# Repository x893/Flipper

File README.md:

# Flipper
Projects for FlipperZero

CadSoft Eagle

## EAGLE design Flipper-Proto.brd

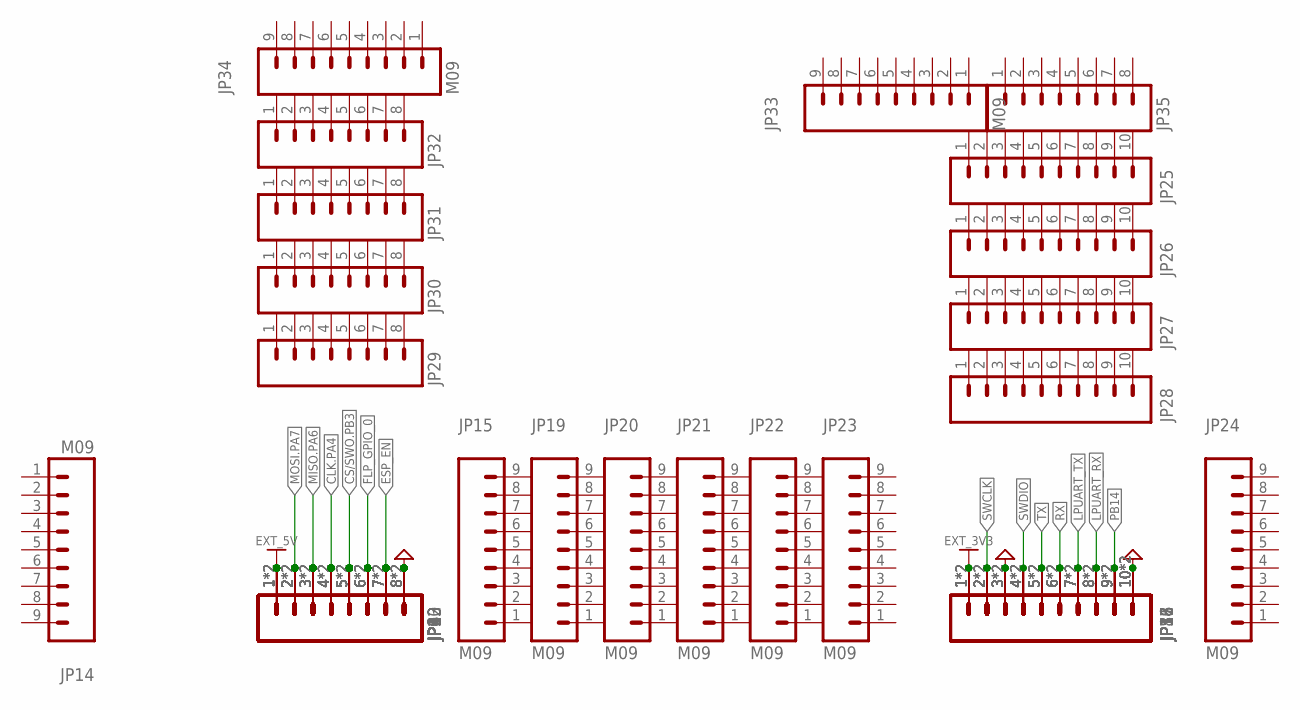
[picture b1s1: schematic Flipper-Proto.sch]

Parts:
JP1, JP11, JP16, JP17, JP18, JP25, JP26, JP27, JP28: M10"; 1X10
JP2, JP3, JP4: M08SMD-COMBO; 1X08_SMD_COMBINED
JP5, JP7, JP8: M10COMBINED; 1X10_SMD_COMBINED
JP6, JP9, JP10, JP12, JP13, JP29, JP30, JP31, JP32, JP35: M081X08; 1X08
JP14, JP15, JP19, JP20, JP21, JP22, JP23, JP24, JP33, JP34: M09; 1X09

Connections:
CLK.PA4: JP2.4, JP2.4@2 (4), JP3.4, JP3.4@2 (4), JP4.4, JP4.4@2 (4), JP6.4, JP9.4, JP10.4, JP12.4, JP13.4
CS/SWO.PB3: JP2.5, JP2.5@2 (5), JP3.5, JP3.5@2 (5), JP4.5, JP4.5@2 (5), JP6.5, JP9.5, JP10.5, JP12.5, JP13.5
ESP_EN: JP2.7, JP2.7@2 (7), JP3.7, JP3.7@2 (7), JP4.7, JP4.7@2 (7), JP6.7, JP9.7, JP10.7, JP12.7, JP13.7
EXT_3V3: JP1.1, JP5.1, JP5.1@2 (1), JP7.1, JP7.1@2 (1), JP8.1, JP8.1@2 (1), JP11.1, JP16.1, JP17.1, JP18.1
EXT_5V: JP2.1, JP2.1@2 (1), JP3.1, JP3.1@2 (1), JP4.1, JP4.1@2 (1), JP6.1, JP9.1, JP10.1, JP12.1, JP13.1
FLP_GPIO_0: JP2.6, JP2.6@2 (6), JP3.6, JP3.6@2 (6), JP4.6, JP4.6@2 (6), JP6.6, JP9.6, JP10.6, JP12.6, JP13.6
GND: JP1.3, JP1.10, JP2.8, JP2.8@2 (8), JP3.8, JP3.8@2 (8), JP4.8, JP4.8@2 (8), JP5.3, JP5.3@2 (3), JP5.10, JP5.10@2 (10), JP6.8, JP7.3, JP7.3@2 (3), JP7.10, JP7.10@2 (10), JP8.3, JP8.3@2 (3), JP8.10, JP8.10@2 (10), JP9.8, JP10.8, JP11.3, JP11.10, JP12.8, JP13.8, JP16.3, JP16.10, JP17.3, JP17.10, JP18.3, JP18.10
LPUART_RX: JP1.8, JP5.8, JP5.8@2 (8), JP7.8, JP7.8@2 (8), JP8.8, JP8.8@2 (8), JP11.8, JP16.8, JP17.8, JP18.8
LPUART_TX: JP1.7, JP5.7, JP5.7@2 (7), JP7.7, JP7.7@2 (7), JP8.7, JP8.7@2 (7), JP11.7, JP16.7, JP17.7, JP18.7
MISO.PA6: JP2.3, JP2.3@2 (3), JP3.3, JP3.3@2 (3), JP4.3, JP4.3@2 (3), JP6.3, JP9.3, JP10.3, JP12.3, JP13.3
MOSI.PA7: JP2.2, JP2.2@2 (2), JP3.2, JP3.2@2 (2), JP4.2, JP4.2@2 (2), JP6.2, JP9.2, JP10.2, JP12.2, JP13.2
PB14: JP1.9, JP5.9, JP5.9@2 (9), JP7.9, JP7.9@2 (9), JP8.9, JP8.9@2 (9), JP11.9, JP16.9, JP17.9, JP18.9
RX: JP1.6, JP5.6, JP5.6@2 (6), JP7.6, JP7.6@2 (6), JP8.6, JP8.6@2 (6), JP11.6, JP16.6, JP17.6, JP18.6
SWCLK: JP1.2, JP5.2, JP5.2@2 (2), JP7.2, JP7.2@2 (2), JP8.2, JP8.2@2 (2), JP11.2, JP16.2, JP17.2, JP18.2
SWDIO: JP1.4, JP5.4, JP5.4@2 (4), JP7.4, JP7.4@2 (4), JP8.4, JP8.4@2 (4), JP11.4, JP16.4, JP17.4, JP18.4
TX: JP1.5, JP5.5, JP5.5@2 (5), JP7.5, JP7.5@2 (5), JP8.5, JP8.5@2 (5), JP11.5, JP16.5, JP17.5, JP18.5

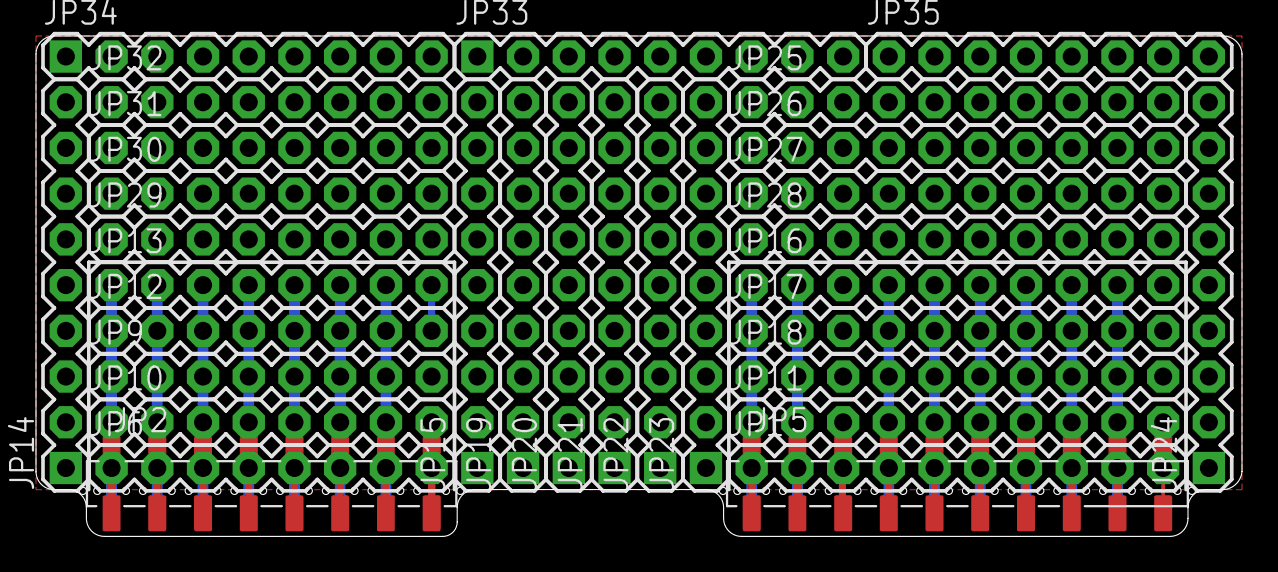
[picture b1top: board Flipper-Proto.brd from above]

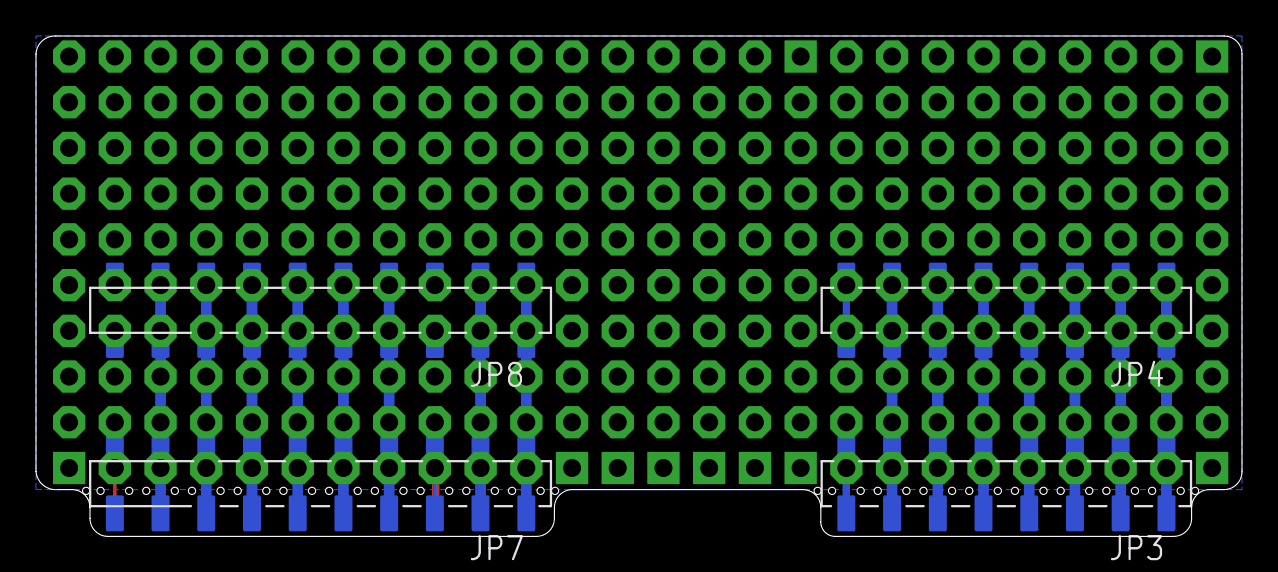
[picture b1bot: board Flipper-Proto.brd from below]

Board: 2 copper layers, 67.0 x 27.8 mm, 35 parts (4 on the bottom side), 16 nets.

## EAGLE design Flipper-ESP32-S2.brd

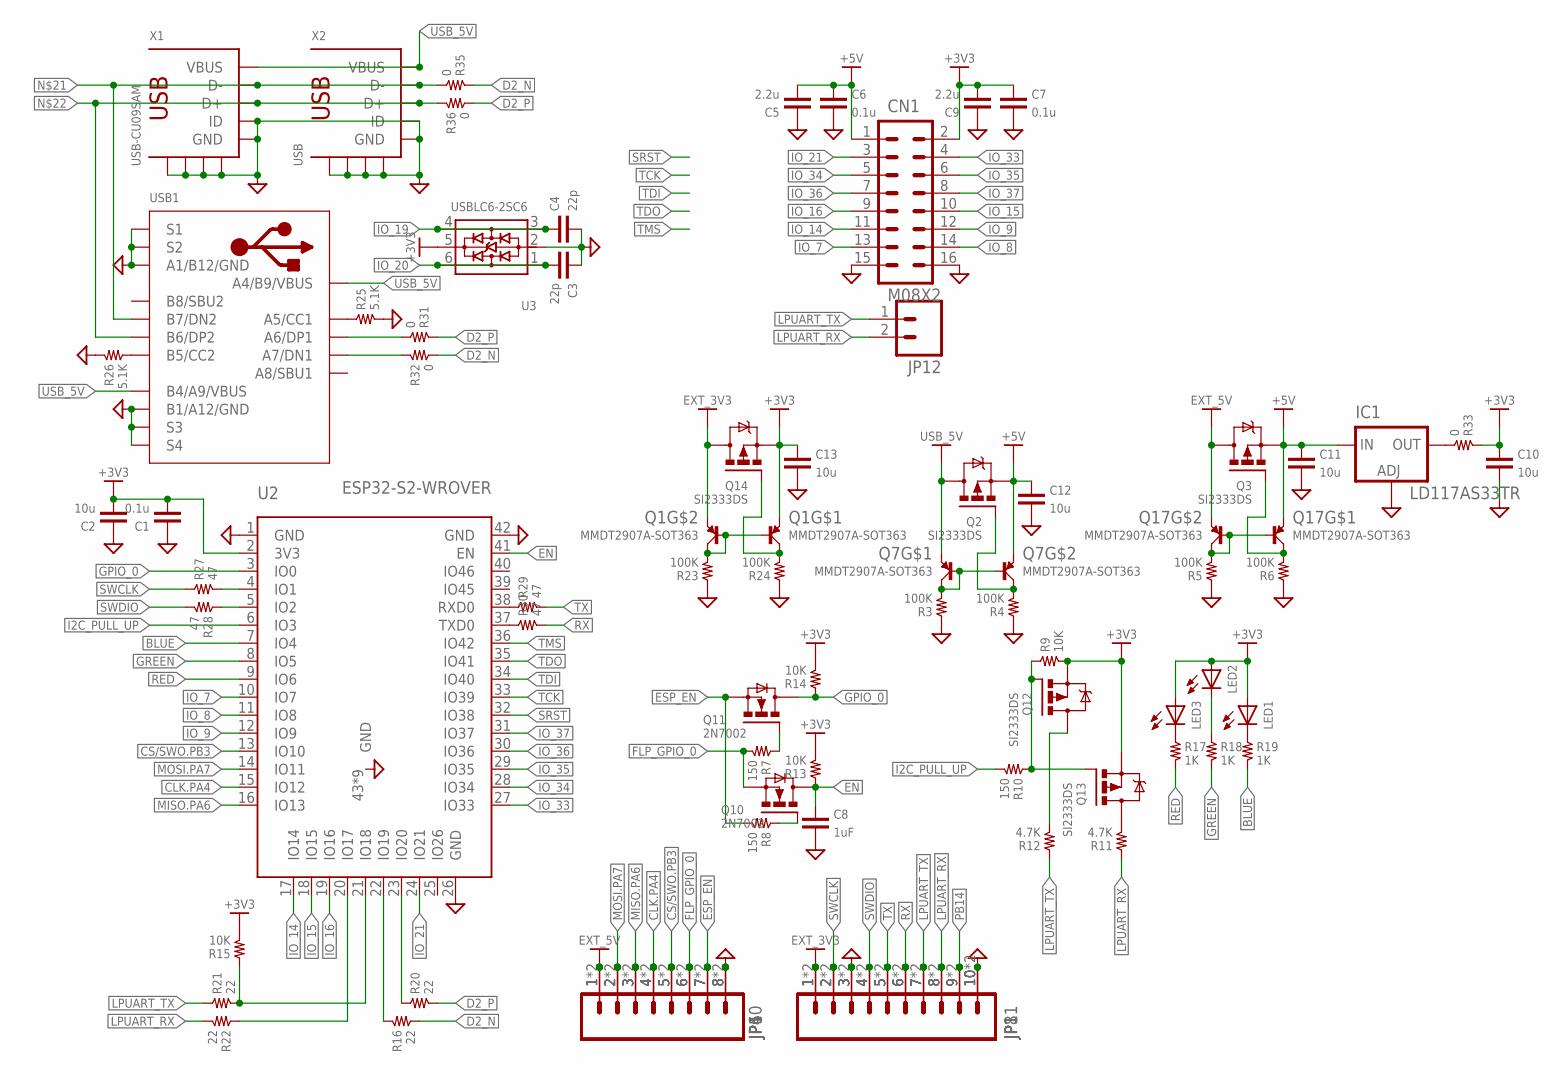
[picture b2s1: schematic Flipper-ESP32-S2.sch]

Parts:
C1, C6, C7: 0.1u; 0603
C2, C10, C11, C12, C13: 10u; 0805
C3, C4: 22p; 0603
C5, C9: 2.2u; 0603
C8: 1uF; 0603
CN1: M08X2; 2X8
IC1: LD117AS33TR; SOT223
JP1, JP11: M10"; 1X10
JP4: M08SMD-COMBO; 1X08_SMD_COMBINED
JP6, JP10: M081X08; 1X08
JP8: M10COMBINED; 1X10_SMD_COMBINED
JP12: M02PTH; 1X02
LED1, LED2, LED3: LEDCHIPLED_0603; CHIPLED_0603
Q1, Q7, Q17: MMDT2907A-SOT363; SOT363
Q2, Q3, Q12, Q13, Q14: SI2333DS; SOT-23
Q10, Q11: 2N7002; SOT-23
R3, R4, R5, R6, R23, R24: 100K; 0603
R7, R8, R10: 150; 0603
R9, R13, R14, R15: 10K; 0603
R11, R12: 4.7K; 0603
R16, R20, R21, R22: 22; 0603
R17, R18, R19: 1K; 0603
R25, R26: 5.1K; 0603
R27, R28, R29, R30: 47; 0603
R31, R32, R33, R35, R36: 0; 0402
U2: ESP32-S2-WROVER
U3: USBLC6-2SC6; SOT23-6
USB1: USB2.0-TYPE-C
X1: USB-CU09SAM; CU09SAM
X2: USB; 473460001

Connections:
5V: C5.1, C6.2, C11.2, C12.2, CN1.1, IC1.3 (IN), Q2.2 (S), Q3.2 (S), Q7.4 (E), Q17.1 (E)
+3V3: C1.1, C2.1, C7.2, C9.1, C10.2, C13.2, CN1.2, LED1.A, LED2.A, LED3.A, Q1.1 (E), Q12.2 (S), Q13.2 (S), Q14.2 (S), R9.2, R13.2, R14.2, R15.2, R33.1, U2.2 (3V3), U3.5 (VBUS)
BLUE: R19.2, U2.7 (IO4)
CLK.PA4: JP4.4, JP4.4@2 (4), JP6.4, JP10.4, U2.15 (IO12)
CS/SWO.PB3: JP4.5, JP4.5@2 (5), JP6.5, JP10.5, U2.13 (IO10)
D2_N: R16.2, R32.2, R35.1
D2_P: R20.2, R31.1, R36.2
EN: C8.2, Q10.3 (D), R13.1, U2.41 (EN)
ESP_EN: JP4.7, JP4.7@2 (7), JP6.7, JP10.7, Q11.2 (S), R8.2
EXT_3V3: JP1.1, JP8.1, JP8.1@2 (1), JP11.1, Q1.4 (E), Q14.3 (D)
EXT_5V: JP4.1, JP4.1@2 (1), JP6.1, JP10.1, Q3.3 (D), Q17.4 (E)
FLP_GPIO_0: JP4.6, JP4.6@2 (6), JP6.6, JP10.6, Q10.2 (S), R7.2
GND: C1.2, C2.2, C3.2, C4.1, C5.2, C6.1, C7.1, C8.1, C9.2, C10.1, C11.1, C12.1, C13.1, CN1.15, CN1.16, IC1.1 (ADJ), JP1.3, JP1.10, JP4.8, JP4.8@2 (8), JP6.8, JP8.3, JP8.3@2 (3), JP8.10, JP8.10@2 (10), JP10.8, JP11.3, JP11.10, R3.1, R4.1, R5.1, R6.1, R23.1, R24.1, R25.2, R26.1, U2.1 (GND), U2.26 (GND), U2.42 (GND), U2.43 (GND), U2.44 (GND), U2.45 (GND), U2.46 (GND), U2.47 (GND), U2.48 (GND), U2.49 (GND), U2.50 (GND), U2.51 (GND), U3.2 (GND), USB1.A1_B12 (A1/B12/GND), USB1.B1_A12 (B1/A12/GND), USB1.S1, USB1.S2, USB1.S3, USB1.S4, USB1.S5 (S1), USB1.S6 (S2), X1.4 (ID), X1.5 (GND), X1.GND@1 (GND), X1.GND@2 (GND), X1.GND@3 (GND), X1.GND@4 (GND), X2.4 (ID), X2.5 (GND), X2.EP@1 (GND), X2.EP@2 (GND), X2.EP@3 (GND), X2.EP@4 (GND)
GPIO_0: Q11.3 (D), R14.1, U2.3 (IO0)
GREEN: R18.2, U2.8 (IO5)
I2C_PULL_UP: R10.2, U2.6 (IO3)
IO_7: CN1.13, U2.10 (IO7)
IO_8: CN1.14, U2.11 (IO8)
IO_9: CN1.12, U2.12 (IO9)
IO_14: CN1.11, U2.17 (IO14)
IO_15: CN1.10, U2.18 (IO15)
IO_16: CN1.9, U2.19 (IO16)
IO_17: R22.1, U2.20 (IO17)
IO_18: R15.1, R21.2, U2.21 (IO18)
IO_19: C4.2, R16.1, U2.22 (IO19), U3.3 (IO2), U3.4 (IO2)
IO_20: C3.1, R20.1, U2.23 (IO20), U3.1 (IO1), U3.6 (IO1)
IO_21: CN1.3, U2.24 (IO21)
IO_33: CN1.4, U2.27 (IO33)
IO_34: CN1.5, U2.28 (IO34)
IO_35: CN1.6, U2.29 (IO35)
IO_36: CN1.7, U2.30 (IO36)
IO_37: CN1.8, U2.31 (IO37)
LPUART_RX: JP1.8, JP8.8, JP8.8@2 (8), JP11.8, JP12.2, R11.1, R22.2
LPUART_TX: JP1.7, JP8.7, JP8.7@2 (7), JP11.7, JP12.1, R12.1, R21.1
MISO.PA6: JP4.3, JP4.3@2 (3), JP6.3, JP10.3, U2.16 (IO13)
MOSI.PA7: JP4.2, JP4.2@2 (2), JP6.2, JP10.2, U2.14 (IO11)
unnamed: Q1.2 (B), Q1.3 (C), Q1.5 (B), R23.2
unnamed: Q1.6 (C), Q14.1 (G), R24.2
unnamed: R29.1, U2.38 (RXD0)
unnamed: LED1.C, R19.1
unnamed: LED3.C, R17.1
unnamed: LED2.C, R18.1
unnamed: R27.2, U2.4 (IO1)
unnamed: Q12.1 (G), Q13.1 (G), R9.1, R10.1
unnamed: Q12.3 (D), R12.2
unnamed: Q13.3 (D), R11.2
unnamed: R28.1, U2.5 (IO2)
unnamed: R30.1, U2.37 (TXD0)
unnamed: IC1.2 (OUT), IC1.4 (OUT), R33.2
unnamed: R32.1, USB1.A7 (A7/DN1)
unnamed: R25.1, USB1.A5 (A5/CC1)
unnamed: R26.2, USB1.B5 (B5/CC2)
unnamed: R31.2, USB1.A6 (A6/DP1)
unnamed: Q11.1 (G), R7.1
unnamed: R35.2, USB1.B7 (B7/DN2), X1.2 (D-), X2.2 (D-)
unnamed: R36.1, USB1.B6 (B6/DP2), X1.3 (D+), X2.3 (D+)
unnamed: Q10.1 (G), R8.1
unnamed: Q7.2 (B), Q7.5 (B), Q7.6 (C), R3.2
unnamed: Q2.1 (G), Q7.3 (C), R4.2
unnamed: Q17.2 (B), Q17.3 (C), Q17.5 (B), R5.2
unnamed: Q3.1 (G), Q17.6 (C), R6.2
PB14: JP1.9, JP8.9, JP8.9@2 (9), JP11.9
RED: R17.2, U2.9 (IO6)
RX: JP1.6, JP8.6, JP8.6@2 (6), JP11.6, R30.2
SRST: U2.32 (IO38)
SWCLK: JP1.2, JP8.2, JP8.2@2 (2), JP11.2, R27.1
SWDIO: JP1.4, JP8.4, JP8.4@2 (4), JP11.4, R28.2
TCK: U2.33 (IO39)
TDI: U2.34 (IO40)
TDO: U2.35 (IO41)
TMS: U2.36 (IO42)
TX: JP1.5, JP8.5, JP8.5@2 (5), JP11.5, R29.2
USB_5V: Q2.3 (D), Q7.1 (E), USB1.A4_B9 (A4/B9/VBUS), USB1.B4_A9 (B4/A9/VBUS), X1.1 (VBUS), X2.1 (VBUS)

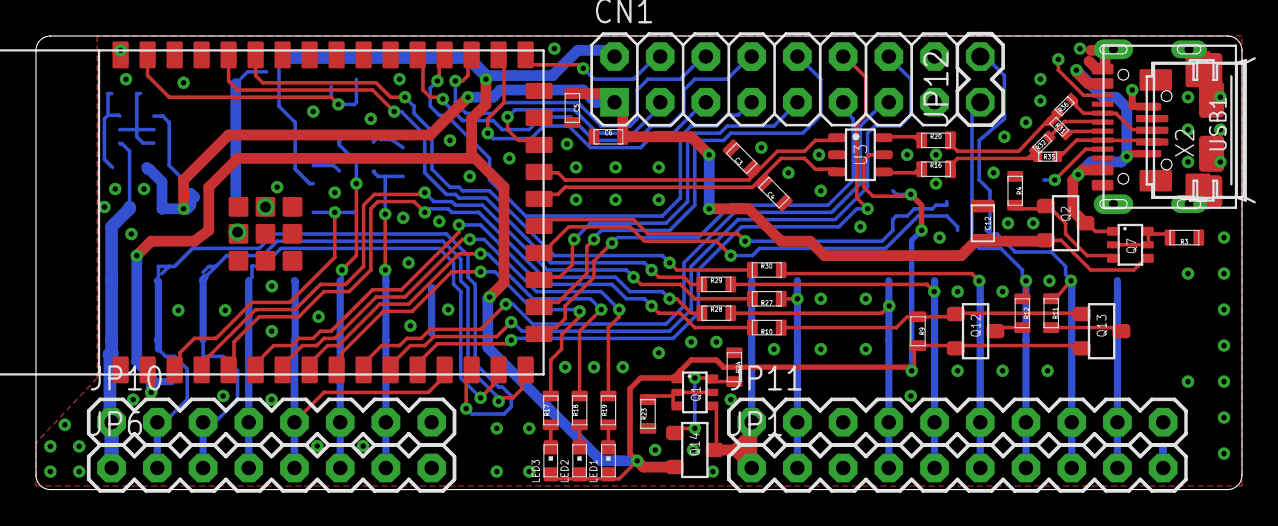
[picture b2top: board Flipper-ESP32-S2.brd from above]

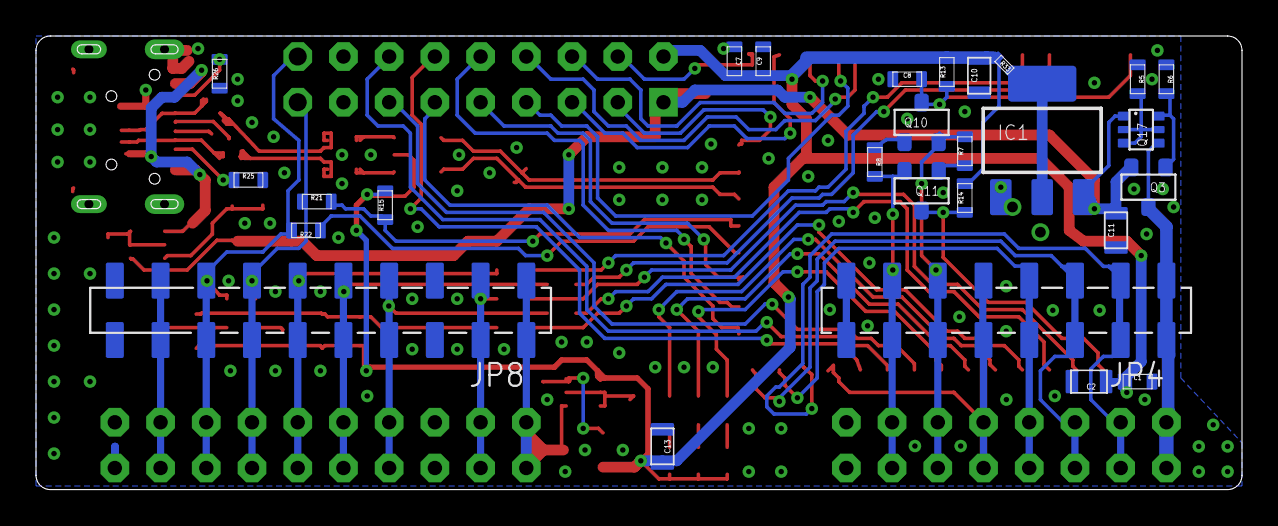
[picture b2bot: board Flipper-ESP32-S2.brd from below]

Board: 2 copper layers, 67.0 x 25.2 mm, 73 parts (27 on the bottom side), 68 nets.

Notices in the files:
parts and their libraries:
SparkFun-Connectors: Licensing: CC v3.0 Share-Alike You are welcome to use this library for commercial purposes.
TL-WR703N: Copyright © 2012, Michel Stempin, All rights reserved
Licenced under Creative Commons CC BY-SA 3.0 license.
